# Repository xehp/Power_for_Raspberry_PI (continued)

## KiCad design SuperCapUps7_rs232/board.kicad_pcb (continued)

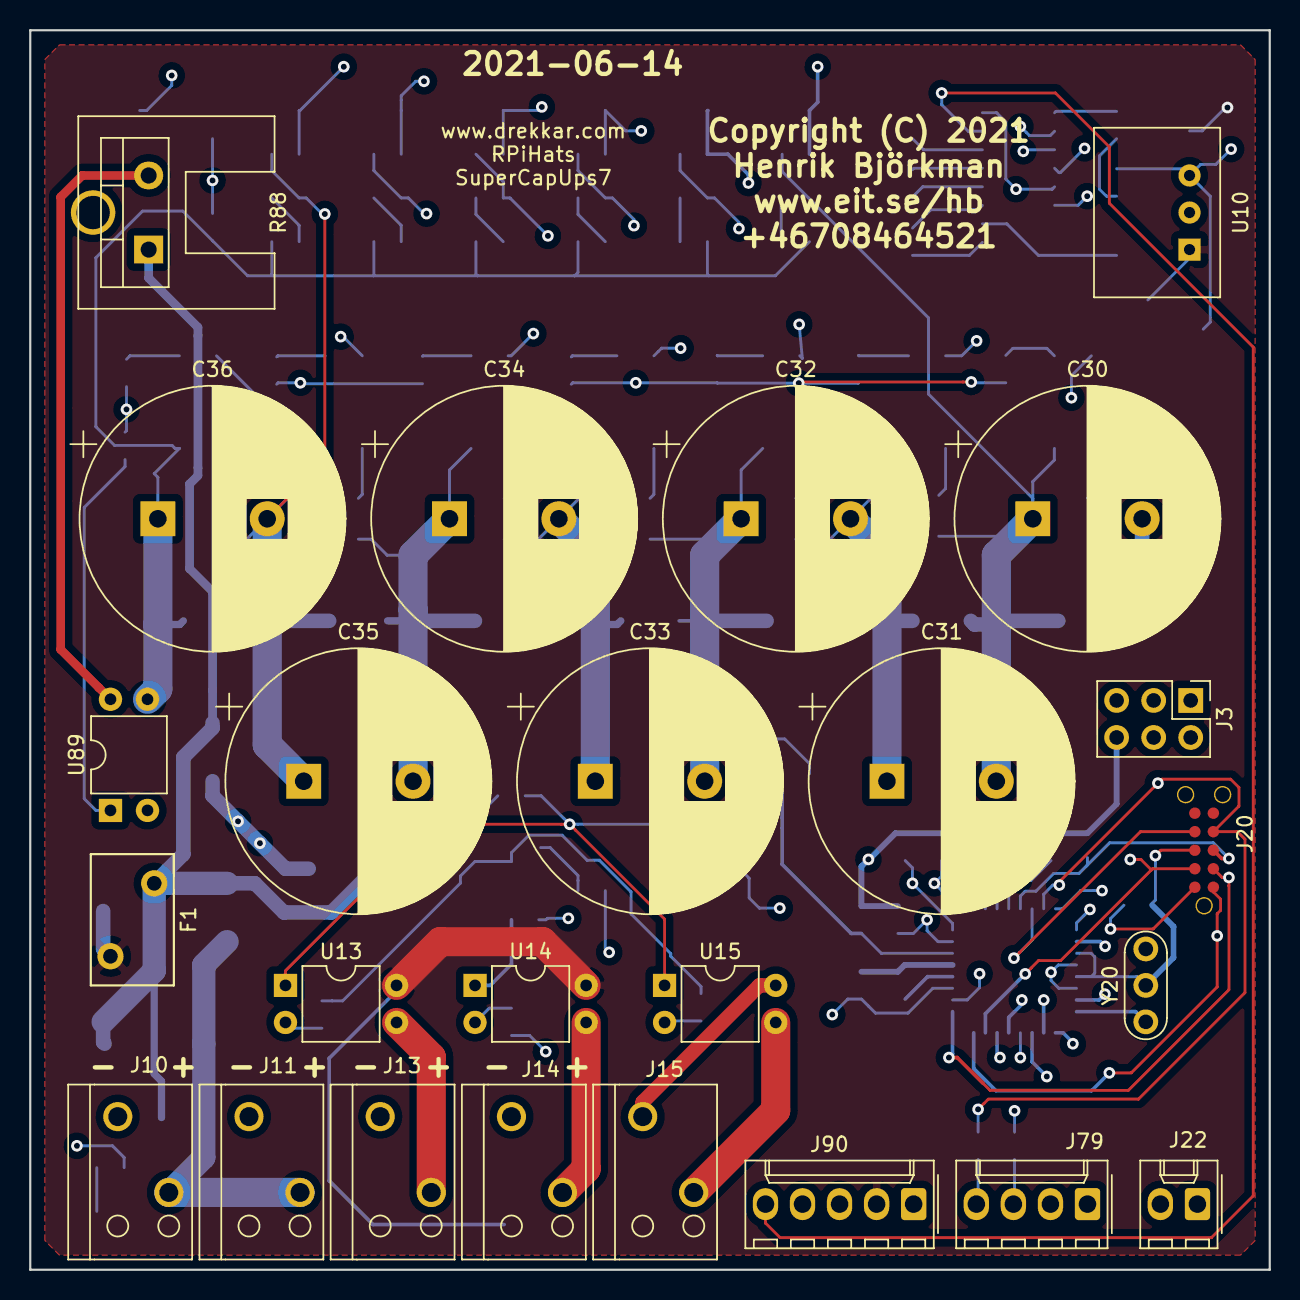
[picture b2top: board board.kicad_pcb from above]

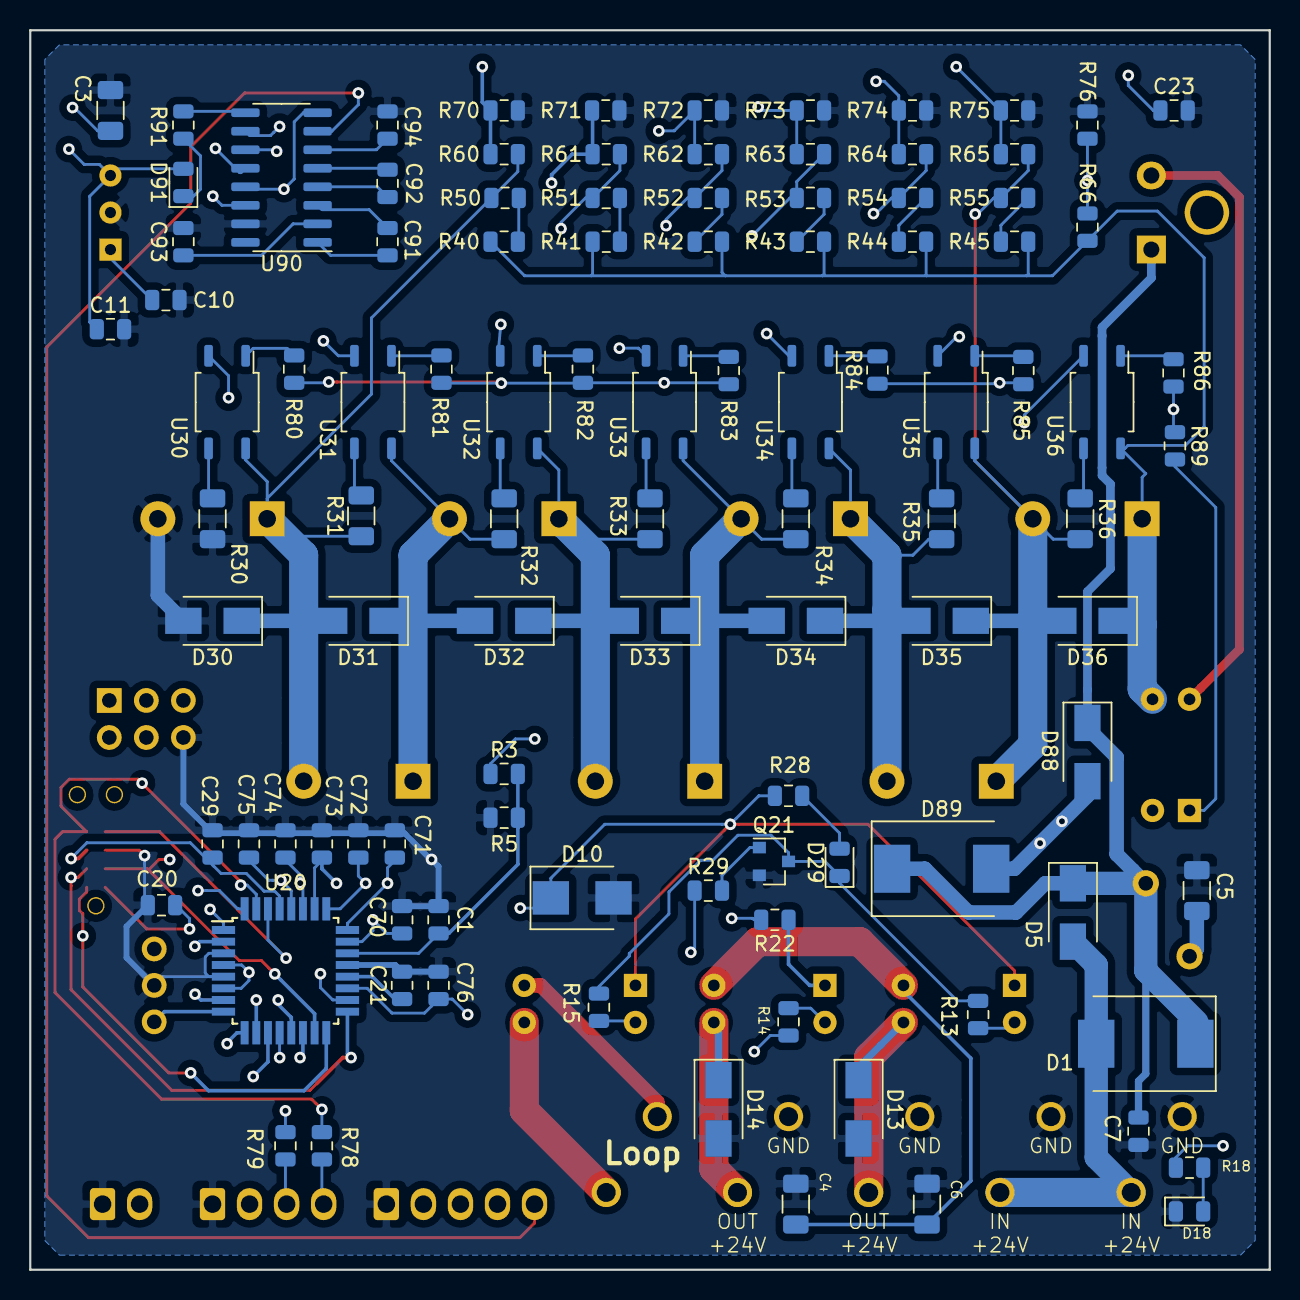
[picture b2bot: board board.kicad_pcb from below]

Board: 4 copper layers, 85.0 x 85.0 mm, 128 parts (103 on the bottom side), 84 nets.

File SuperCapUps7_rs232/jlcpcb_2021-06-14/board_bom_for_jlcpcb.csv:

Comment,Designator,Footprint,LCSC
"1uF","C1,C7,C10,C11,C23,C70,C71,C72,C73,C74,C75,C76","Capacitor_SMD:C_0805_2012Metric",""
"0.1uF","C20,C21,C29,C91,C92,C93,C94","Capacitor_SMD:C_0805_2012Metric",""
"CP","C30,C31,C32,C33,C34,C35,C36","Capacitor_THT:CP_Radial_D18.0mm_P7.50mm",""
"10uF","C3,C4,C5,C6","Capacitor_SMD:C_1206_3216Metric",""
"D_Zener","D10","Diode_SMD:D_SMB",""
"red","D18","LED_SMD:LED_0805_2012Metric",""
"green","D29","LED_SMD:LED_0805_2012Metric",""
"D","D5,D13,D14,D30,D31,D32,D33,D34,D35,D36,D88","Diode_SMD:D_SMA",""
"D","D1,D89","Diode_SMD:D_SMC",""
"amber","D91","LED_SMD:LED_0805_2012Metric",""
"Fuse-Device","F1","eit_footprints:Varistor_RV_Disc_D9mm_W5.7mm_P5mm",""
"Conn_01x02","J10,J11,J13,J14,J15","eit_footprints:connector_TE_Connectivity_2_pin",""
"connector_10pin_ISP_Console","J20","eit_footprints:connector_10pin_TC2050-IDC-NL",""
"Conn_01x02","J22","Connector_Molex:Molex_KK-254_AE-6410-02A_1x02_P2.54mm_Vertical",""
"Conn_02x03_Odd_Even","J3","Connector_PinHeader_2.54mm:PinHeader_2x03_P2.54mm_Vertical",""
"Conn_01x04","J79","Connector_Molex:Molex_KK-254_AE-6410-04A_1x04_P2.54mm_Vertical",""
"Conn_01x05","J90","Connector_Molex:Molex_KK-254_AE-6410-05A_1x05_P2.54mm_Vertical",""
"S8050","Q21","Package_TO_SOT_SMD:SOT-23",""
"10K","R22","Resistor_SMD:R_0805_2012Metric",""
"470","R28","Resistor_SMD:R_0805_2012Metric",""
"1K","R29","Resistor_SMD:R_0805_2012Metric",""
"100","R30,R31,R32,R33,R34,R35,R36","Resistor_SMD:R_1206_3216Metric",""
"47K","R43,R50","Resistor_SMD:R_0805_2012Metric",""
"3.3K","R5","Resistor_SMD:R_0805_2012Metric",""
"4K7","R53","Resistor_SMD:R_0805_2012Metric",""
"6K8","R54","Resistor_SMD:R_0805_2012Metric",""
"2K2","R55","Resistor_SMD:R_0805_2012Metric",""
"22K","R45,R51,R52,R60","Resistor_SMD:R_0805_2012Metric",""
"33K","R44,R61","Resistor_SMD:R_0805_2012Metric",""
"68K","R42,R62,R63","Resistor_SMD:R_0805_2012Metric",""
"100K","R40,R41,R64","Resistor_SMD:R_0805_2012Metric",""
"150K","R3,R65","Resistor_SMD:R_0805_2012Metric",""
"220K","R66","Resistor_SMD:R_0805_2012Metric",""
"3K3","R70,R71,R72,R73,R74,R75,R76","Resistor_SMD:R_0805_2012Metric",""
"27","R78,R79","Resistor_SMD:R_0805_2012Metric",""
"220","R13,R14,R15,R18,R80,R81,R82,R83,R84,R85,R86,R89,R91","Resistor_SMD:R_0805_2012Metric",""
"33 Ohm, >=10 W","R88","eit_footprints:TO-220-2_with_heatsink_V8508B",""
"3.3 Volt","U10","eit_footprints:DC-DC-Recom-R78",""
"ATmega328-AU","U20","Package_QFP:TQFP-32_7x7mm_P0.8mm",""
"opto_coupler_EL357N(B)(TA)-G","U30,U31,U32,U33,U34,U35,U36","eit_footprints:SOP-4_4.1x4.4x2.54P",""
"TLP222A","U13,U14,U15,U89","Package_DIP:DIP-4_W7.62mm",""
"MAX232","U90","Package_SO:SOIC-16_3.9x9.9mm_P1.27mm",""
"Crystal_GND2","Y20","Crystal:Resonator-3Pin_W7.0mm_H2.5mm",""

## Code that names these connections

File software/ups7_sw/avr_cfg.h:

/*
avr_cfg.h

provide functions to configure SW to match hardware

Copyright (C) 2021 Henrik Bjorkman www.eit.se/hb.

This file is free software; you can redistribute it and/or modify it
under the terms of the GNU Lesser General Public License version 2.1.

Removing this comment or the history section is not allowed.
If you modify this code make a note about it in the history
section below. That is required!

This program is distributed in the hope that it will be useful, but
WITHOUT ANY WARRANTY; without even the implied warranty of
MERCHANTABILITY or FITNESS FOR A PARTICULAR PURPOSE.  See the GNU
General Public License for more details.

History

2005-03-23 Created by Henrik Bjorkman
2021-04-20 Updated. /Henrik
*/


#ifndef AVR_CFG_H
#define AVR_CFG_H

// Use 0 or 1 here
// For HW 2021-04-05 use HW_VERSION 0
// For HW 2021-04-23 or 2021-04-27 use 1
// For HW 2021-05-27 use HW_VERSION 2 (wrong transistor was used)
// For HW after 2021-05-27 it is so far HW_VERSION 1 to use.
#define HW_VERSION 2

#define AVR_FOSC 7370000

// If FOSC is 16 MHz and 115200 is selected here we get 118000 baud instead.
#define UART_BAUDRATE 115200


// Using pin PD3 for debug LED
#define DEBUG_LED_DDR DDRB
#define DEBUG_LED_PORT PORTB
#define DEBUG_LED_BIT PB5
#define DEBUG_LED_ACTIVE_HIGH

// Using pin PD3 for charging indication LEDs
//#define POWER_LED_DDR DDRD
//#define POWER_LED_PORT PORTD
//#define POWER_LED_BIT PD3


// Configure timer use. Make sure to use each timer for only one thing.


// We can use timer0 or timer2 as system clock
// Uncomment one of these:
//#define AVR_SYS_USE_TMR0
#define AVR_SYS_USE_TMR2




// Configuration of IO pins

#define RELAY_CHARGE_DDR DDRD
#define RELAY_CHARGE_PORT PORTD
#define RELAY_CHARGE_BIT PD7
#define RELAY_CHARGE_ACTIVE_LOW


#define RELAY_LOOP_DDR DDRB
#define RELAY_LOOP_PORT PORTB
#define RELAY_LOOP_BIT PB5
#define RELAY_LOOP_ACTIVE_HIGH


#define RELAY_MAIN_DDR DDRB
#define RELAY_MAIN_PORT PORTB
#define RELAY_MAIN_BIT PB2
#define RELAY_MAIN_ACTIVE_LOW



#define RELAY_SHUNT0_DDR DDRB
#define RELAY_SHUNT0_PORT PORTB
#define RELAY_SHUNT0_BIT PB0
#define RELAY_SHUNT0_ACTIVE_LOW

#define RELAY_SHUNT1_DDR DDRB
#define RELAY_SHUNT1_PORT PORTB
#define RELAY_SHUNT1_BIT PB1
#define RELAY_SHUNT1_ACTIVE_LOW

#define RELAY_SHUNT2_DDR DDRD
#define RELAY_SHUNT2_PORT PORTD
#define RELAY_SHUNT2_BIT PD2
#define RELAY_SHUNT2_ACTIVE_LOW

#define RELAY_SHUNT3_DDR DDRD
#define RELAY_SHUNT3_PORT PORTD
#define RELAY_SHUNT3_BIT PD3
#define RELAY_SHUNT3_ACTIVE_LOW

#define RELAY_SHUNT4_DDR DDRD
#define RELAY_SHUNT4_PORT PORTD
#define RELAY_SHUNT4_BIT PD4
#define RELAY_SHUNT4_ACTIVE_LOW

#define RELAY_SHUNT5_DDR DDRD
#define RELAY_SHUNT5_PORT PORTD
#define RELAY_SHUNT5_BIT PD5
#define RELAY_SHUNT5_ACTIVE_LOW

#define RELAY_SHUNT6_DDR DDRD
#define RELAY_SHUNT6_PORT PORTD
#define RELAY_SHUNT6_BIT PD6
#define RELAY_SHUNT6_ACTIVE_LOW



#define RELAY_EXT_DDR DDRB
#define RELAY_EXT_PORT PORTB
#define RELAY_EXT_BIT PB3
#define RELAY_EXT_ACTIVE_LOW



// Input for trigger button, PC2
// NOTE in next HW version 2021-04-24 and later trigger will be active high
#define TRIGGER_PORT PORTB
#define TRIGGER_PORT_PIN PINB
#define TRIGGER_BIT PB4
#define TRIGGER_ACTIVE_LOW



// Using pin PD3 for charging indication LEDs
// Active for serial port is a zero out.
//#define SOFT_UART_TXD_DDR DDRD
//#define SOFT_UART_TXD_PORT PORTD
//#define SOFT_UART_TXD_BIT PD3
//#define SOFT_UART_TXD_ACTIVE_LOW

// Using pin PD3 for charging indication LEDs
// Active for serial port is a zero out.
//#define SOFT_UART_RXD_DDR DDRD
//#define SOFT_UART_RXD_PIN PINB
//#define SOFT_UART_RXD_PORT PORTD
//#define SOFT_UART_RXD_BIT PD2
//#define SOFT_UART_RXD_ACTIVE_LOW

#endif

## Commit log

2021-09-27 copied files over from the RPi_HATs repository
2021-10-06 This version was tested and something failed, see SuperCapUps7_rs232/bom.txt for details
